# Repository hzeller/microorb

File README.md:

Microorb
========

A USB connected high-power RGB LED. Before there were cheap RGB devices for
USB, this is what we used to show continuous build status on the developers'
workstations.

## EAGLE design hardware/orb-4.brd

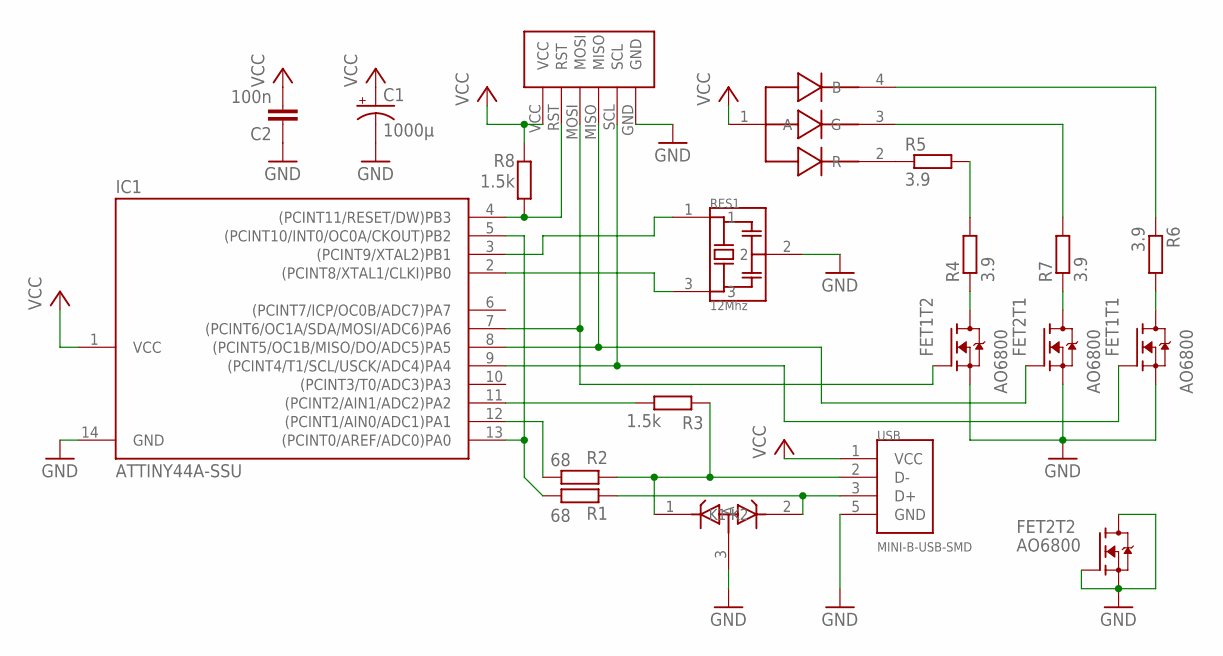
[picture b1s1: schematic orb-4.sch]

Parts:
C1: 1000µ; PANASONIC_F
C2: 100n; C0805K
D1: 3.6V; SOT23
FET1, FET2: AO6800; TSOP6
IC1: ATTINY44A-SSU; SOIC14
R1, R2: 68; M0805
R3, R8: 1.5k; M0805
R4, R5, R6, R7: 3.9; R2512
RES1: 12Mhz; AWSCR-CV
U$1: 5W-RGB; 5W-POWER-LED
U$2: PROG-HEADER; SMALL-PROG-HEADER
USB: MINI-B-USB-SMD; USB-UX60SC-SMD

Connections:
D+: D1.2 (K2), R1.1, USB.3 (D+)
D-: D1.1 (K1), R2.1, R3.2, USB.2 (D-)
GND: C1.-, C2.1, D1.3 (A), FET1.2 (S), FET1.5 (S), FET2.2 (S), FET2.3 (G), FET2.4 (D), FET2.5 (S), IC1.14 (GND), RES1.2, U$2.GND, USB.5 (GND)
unnamed: IC1.2 ((PCINT8/XTAL1/CLKI)PB0), RES1.3
unnamed: IC1.3 ((PCINT9/XTAL2)PB1), RES1.1
unnamed: FET1.3 (G), IC1.7 ((PCINT6/OC1A/SDA/MOSI/ADC6)PA6), U$2.MOSI
unnamed: IC1.11 ((PCINT2/AIN1/ADC2)PA2), R3.1
unnamed: IC1.5 ((PCINT10/INT0/OC0A/CKOUT)PB2), IC1.13 ((PCINT0/AREF/ADC0)PA0), R1.2
unnamed: IC1.12 ((PCINT1/AIN0/ADC1)PA1), R2.2
unnamed: FET1.4 (D), R4.1
unnamed: FET2.6 (D), R7.1
unnamed: FET1.6 (D), R6.2
unnamed: R5.1, U$1.2 (R)
unnamed: R7.2, U$1.3 (G)
unnamed: R6.1, U$1.4 (B)
unnamed: FET2.1 (G), IC1.8 ((PCINT5/OC1B/MISO/DO/ADC5)PA5), U$2.MISO
unnamed: FET1.1 (G), IC1.9 ((PCINT4/T1/SCL/USCK/ADC4)PA4), U$2.SCL
unnamed: R4.2, R5.2
RESET: IC1.4 ((PCINT11/RESET/DW)PB3), R8.1, U$2.RST
VCC: C1.+, C2.2, IC1.1 (VCC), R8.2, U$1.1 (A), U$2.VCC, USB.1 (VCC)

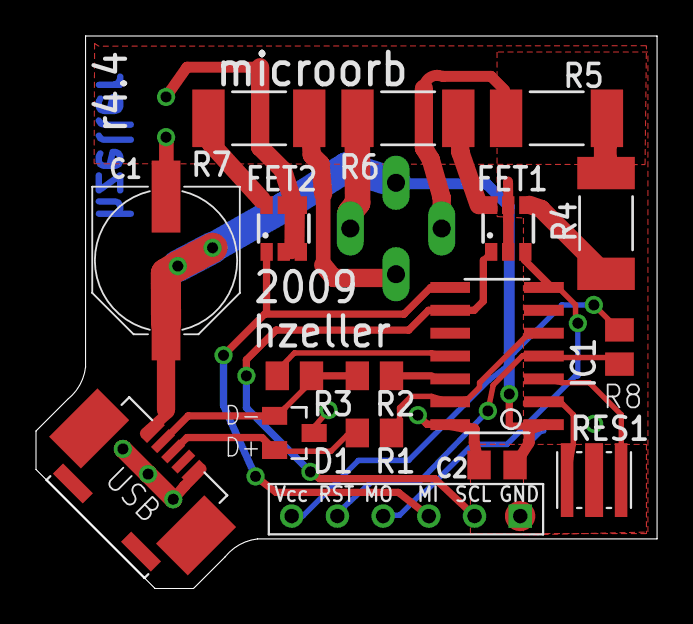
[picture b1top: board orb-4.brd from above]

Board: 2 copper layers, 34.5 x 30.7 mm, 18 parts (1 on the bottom side), 20 nets.

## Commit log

2009-04-27 o initial.
2009-04-30 o update protocol description.
2009-08-14 o Unsuccessful attempt to do two-segment two OCA/OCB timer thing. Too much problems with timing of close events.
2009-09-04 o Switch to new 'final' hardware layout (some bits shifted) o start moving PWM back in the main loop. The timing won't work.
2009-09-17 o First version of morphing with 32bit calculation.
2009-09-21 o Add simplified gamma correction.
2009-09-25 o ups, last segment was not there, so we were reading random RAM crap.
2009-09-26 o more sequence elements o setting a new sequence will start with it right away (not completely cool yet: it starts with the last color in the sequence)
2009-09-26 o increase device version to 1.04 so that hostprogram can detect that no current limiting is necessary. o Increase sequence len to 8 o Init google startup sequence.
2009-09-28 o make #defines for ports enums. o current limiting to 500mA o 'white' balance: limit current of blue.
2009-09-28 o Extend sequence to 10 elements o Make default sequence wait for some more time. o Handle buffer overflow attempt gracefully.
2009-09-29 o make writing sequence buffer-overflow safe.
2009-09-30 o first attempt to set the serial number in eeprom. Now we're using all our space :/
2009-09-30 o store in eeprom - serial number - flag if we should do current limiting - initial sequence o implement 'get_color()'
2009-09-30 o add some comments before adding to perforce.
2009-09-30 o remove irrelevant part of usbtiny-1.4 o add README.orb o add more elements to the black-phase.
2009-09-30 o Update documentation.
2009-09-30 o remove irrelevant stuff from usbtiny-1.4/util
2009-09-30 o add current_limit capability flag.
2009-09-30 o add prototypes to functions. o Name functions consistently so that it is clear what datatype they manipulate ('object oriented in C') o Do fixedpoint arithmetic with a shift of 24 so that a simple 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
2009-09-30 o morph_t -> colormorph_t
2009-09-30 o some more documentation update.
2009-09-30 o Documentation updates.
2009-09-30 o some doc updates.
2009-10-01 o experimental timer testing.
2009-10-01 o provide proper padding for fixvalue register.
2009-10-01 o only set pwm_segments[3] once.
2009-10-01 o temporary state: debugging why usb protocol errors occur sometime.
2009-10-01 o use less memory. Looks like we were using too much (usb stopped working) o stray in some usb_poll()'s
2009-10-02 o USB speed improvements. Mostly by Zoltan.
2009-10-10 o simplify code a bit (no LT comparision but NE 0) o add AUX bit again for debugging.
2009-10-12 o Provide set-aux feature.
2009-10-12 o Implement get_sequence. o Simplify buffer overflow handling.
2009-10-12 o simplify setting output
2009-10-12 o check the current limit bit after setting eeprom. That way we don't have to reset the orb for the limit to become active. o initial sequence a bit more often. o use timer by default.
2009-10-12 o start from current color for sequence.
2009-10-12 o some comment changes.
2009-10-12 o update fuses in Makefile.
2010-02-21 o add todo.txt
2010-02-21 o move firmware to ... firmware.
2010-02-21 o move orb4-firmware to just firmware o add usb-host
2010-02-22 o extract protocol specific stuff to microorb-protocol o implement MicroOrb c++ class of the orb.
2010-02-22 o Use common microorb-protocol.h for firmware and host-software.
2010-02-22 o More documentation.
2010-02-22 o Extract sequence parsing out of main(). More documentation.
2010-02-22 o {} instead of single-line if.
2010-02-22 o Add current limiting for older orbs.
2010-02-22 o more documentation for the current limiting.
2010-02-22 o Verify color sequence we sent.
2010-02-22 o some comments.
2010-02-22 o some documentation updates.
2010-02-22 o More documentation upadtes.
2010-02-26 o merge changes from perforce.
2010-02-26 o Show help and list of orbs on empty commandline.
2010-12-19 o Add permanent setting of initial sequence.
2011-09-24 Move all software to 'software' subdirectory.
2011-09-24 Add hardware
2011-10-05 o Re-add reset pull-up. o add revision text (r4.1)
2011-10-05 o change path to new eagle.
2011-10-11 o revision 4.4
2011-10-11 o add measurements and documentation 'layer' o output gerber for it and documentation.
2011-10-11 o have $(FAB_DIR) instead of fab/
2011-10-13 o add usbtiny 1.6 upstream
2011-10-13 o remove uneccessary stuff from usbtiny distribution.
2011-10-13 o Patch usbtiny to support eeprom serial number o use new usbtiny in firmware.
2011-10-13 o remove old usbtiny 1.4
2011-10-13 o comment undocumented feature: setting initial sequenc.
2011-10-13 o update comments for usb_{in,out}()
2011-10-13 o cleanup comment
2011-10-13 o new eagle version.
2011-10-13 o make directory with project name
2011-10-13 o really clean fab and print dir.
2011-10-13 o make dir clean work in case there are no dirs :)
2011-10-25 o add assembly documentation.
2012-01-21 o Add simple factory test function.
2012-01-22 o allow to write the serial number using the microorb API
2012-01-22 o serial number just with generic string.
2012-01-22 o Add a little curses prettiness.
2012-01-22 o Don't continue if prefix in file and commandline mismatch.
2012-01-22 o Externalize light sensor for better implementation.
2012-01-23 o Make things fit in 4k with 4.5 gcc (sigh.)
2012-01-23 o Only sequence of four is reliable.
2012-01-26 o Print fuse.
2012-01-26 o add simple webserver.
2012-01-26 o update README
2012-03-29 o ...
2012-04-11 o derive filename from prefix.
2012-04-11 o Move manual RGB test to the end of the electrical testing.
2012-04-13 o fix typo
2012-04-27 Add port help.
2012-09-08 o fix license
2012-09-08 o Add http comment.
2012-09-08 o update sequence comment.
2012-09-08 o Add logging.
2012-09-08 o rename WriteLog() to WriteHttpLog()
2016-12-11 o make usb tiny compile with current compilers.
2016-12-11 o Some generic start sequence.
2016-12-11 o Some http functions have been marked deprecated in the microhttp in the meantime. Bring up-to-date.
2016-12-11 o some consistent indentation.
2016-12-11 o Update makefile for latest eagle.
2016-12-11 o Load and save eagle files to convert from 5.x version to 7.x version that is XML
2016-12-11 o Initial readme.
2016-12-11 o todone
2016-12-11 o update text.
2021-09-18 Make compile with new microhttp library.
2021-09-18 In the index html, also explain how to invoke URL directly.
2021-09-18 Re-connect to Orb if connection lost.
2021-09-18 Properly return 404 response.
2021-09-18 Make sure to test for existence of orb object after reconnect.
2021-09-20 Don't wait with getchar() in forground.
    This is not a good idea if there is no controlling terminal.
2022-12-27 Adapt to microhttp version.
    Also, add shell.nix
2022-12-27 Add shell.nix dependencies to compile firmware.
